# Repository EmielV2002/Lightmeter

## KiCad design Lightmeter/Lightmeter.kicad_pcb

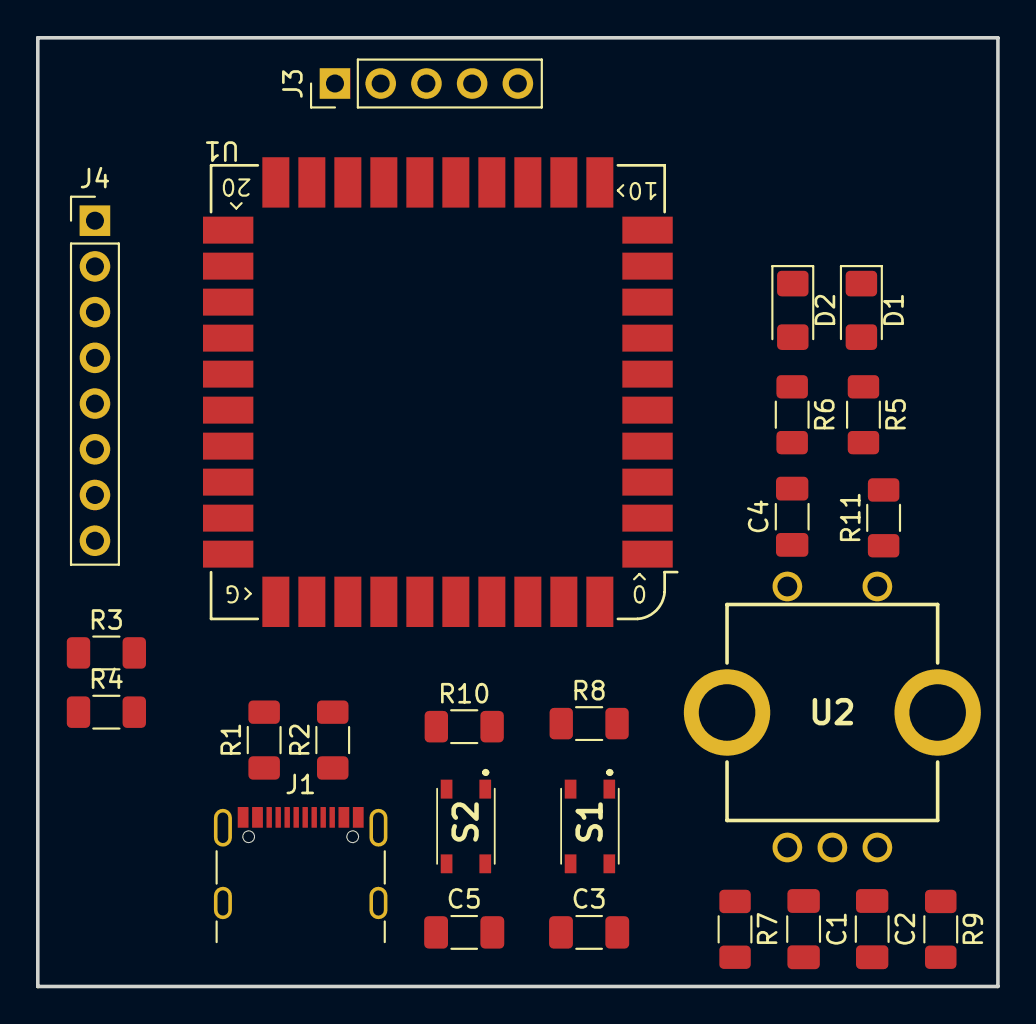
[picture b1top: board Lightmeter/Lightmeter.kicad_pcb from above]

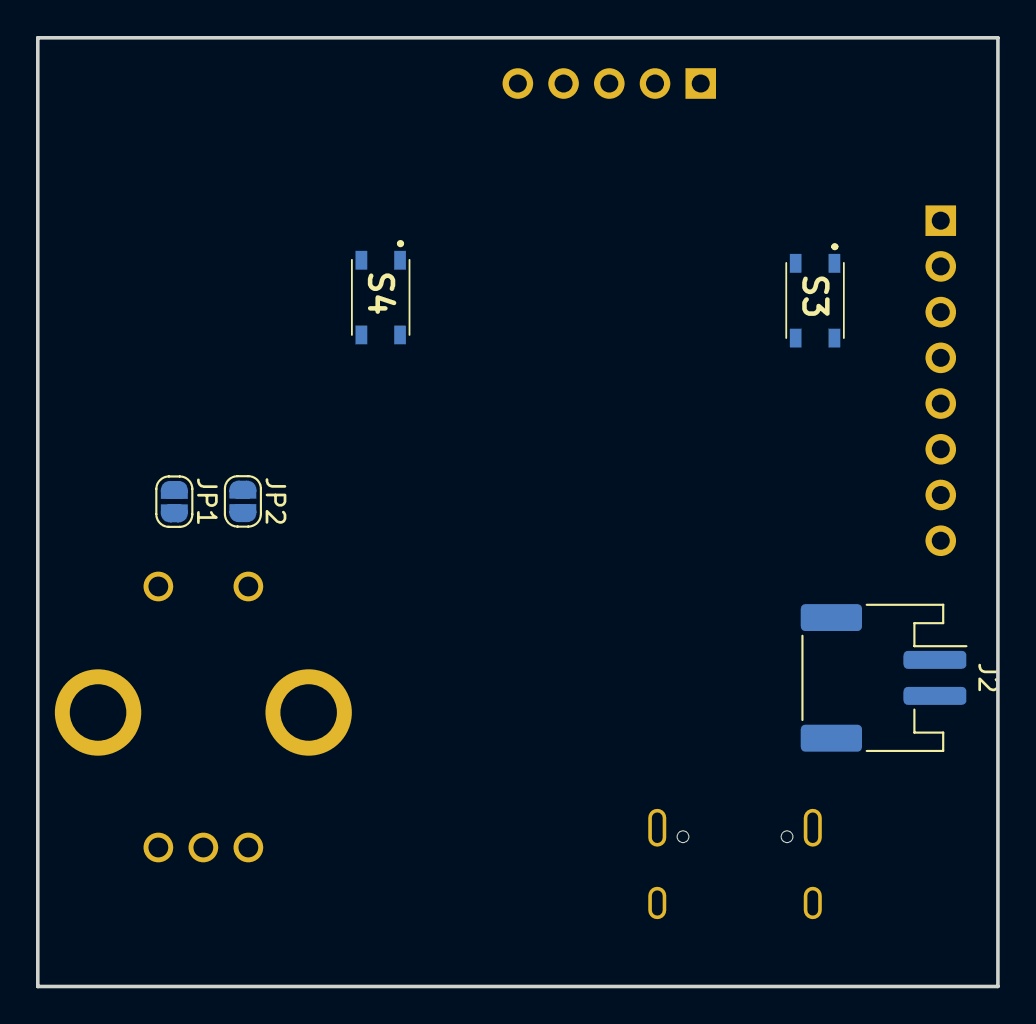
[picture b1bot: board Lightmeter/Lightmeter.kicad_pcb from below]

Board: 2 copper layers, 53.3 x 52.7 mm, 30 parts (5 on the bottom side), 30 nets, no tracks yet.

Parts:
C1, C2, C3, C4, C5: 0.1uF; C_1206_3216Metric_Pad1.33x1.80mm_HandSolder
D1, D2: LED; LED_1206_3216Metric_Pad1.42x1.75mm_HandSolder
J1: USB_C_Receptacle_USB2.0; USB_C_Receptacle_GCT_USB4105-xx-A_16P_TopMnt_Horizontal
J2: Conn_01x02_Socket; JST_PH_S2B-PH-SM4-TB_1x02-1MP_P2.00mm_Horizontal
J3: Conn_01x05_Pin; PinHeader_1x05_P2.54mm_Vertical
J4: Conn_01x08_Socket; PinHeader_1x08_P2.54mm_Vertical
JP1, JP2: Jumper_2_Open; SolderJumper-2_P1.3mm_Open_RoundedPad1.0x1.5mm
R1, R2: 5.1k; R_1206_3216Metric_Pad1.30x1.75mm_HandSolder
R3, R4: 100k; R_1206_3216Metric_Pad1.30x1.75mm_HandSolder
R5, R6: 1k; R_1206_3216Metric_Pad1.30x1.75mm_HandSolder
R7, R8, R9, R10, R11: 10k; R_1206_3216Metric_Pad1.30x1.75mm_HandSolder
S1, S2, S3, S4: PTS810SJK250SMTRLFS; PTS810SJG250SMTRLFS
U1: RP2040_Stamp; RP2040_Stamp_SMD
U2: EC11E1544505

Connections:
+3.3V: J3.5, J4.1, JP1.2 (B), JP2.2 (B), R7.2, R8.1, R9.2, R10.1, R11.2, U1.34 (3.3V)
+BATT: J2.1, R3.1, U1.32 (VBAT)
/BOOTSEL: S3.1, S3.2, U1.40 (BOOTSEL)
/EN_CLK: C1.1, R7.1, U1.8 (GPIO7), U2.1 (A)
/EN_DT: C2.1, R9.1, U1.9 (GPIO8), U2.2 (B)
/EN_SW: C4.1, R11.1, U1.10 (GPIO9), U2.4 (D)
/ISO: R8.2, S1.1, S1.2, U1.24 (GPIO23)
/LED_USR: D2.1 (K), U1.25 (GPIO24)
/L_SCL: J3.3, U1.6 (GPIO5)
/L_SDA: J3.4, U1.5 (GPIO4)
/MEAS: R10.2, S2.1, S2.2, U1.17 (GPIO16)
/SCREEN_CS: J4.6, U1.19 (GPIO18)
/SCREEN_DC: J4.7, U1.22 (GPIO21)
/SCREEN_MOSI: J4.4, U1.21 (GPIO20)
/SCREEN_RST: J4.8, U1.23 (GPIO22)
/SCREEN_SCK: J4.5, U1.20 (GPIO19)
/USB_D+: J1.A6 (D+), J1.B6 (D+), U1.36 (USB_D+)
/USB_D-: J1.A7 (D-), J1.B7 (D-), U1.35 (USB_D-)
/VDIV: R3.2, R4.1, U1.27 (GPIO26)
/~RESET: S4.1, S4.2, U1.39 (~RESET)
GNDREF: C1.2, C2.2, C3.2, C4.2, C5.2, D1.1 (K), J1.A1 (GND), J1.A12 (GND), J1.B1 (GND), J1.B12 (GND), J1.S1 (SHIELD), J2.2, J3.1, J4.2, R1.2, R2.2, R4.2, S3.3, S3.4, S4.3, S4.4, U1.31 (GND), U2.3 (C), U2.5 (E)
unnamed: C3.1, S1.3, S1.4
unnamed: C5.1, S2.3, S2.4
unnamed: D1.2 (A), R5.2
unnamed: D2.2 (A), R6.2
unnamed: J1.A5 (CC1), R1.1
unnamed: J1.B5 (CC2), R2.1
unnamed: JP1.1 (A), R5.1
unnamed: JP2.1 (A), R6.1
VBUS: J1.A4 (VBUS), J1.A9 (VBUS), J1.B4 (VBUS), J1.B9 (VBUS)

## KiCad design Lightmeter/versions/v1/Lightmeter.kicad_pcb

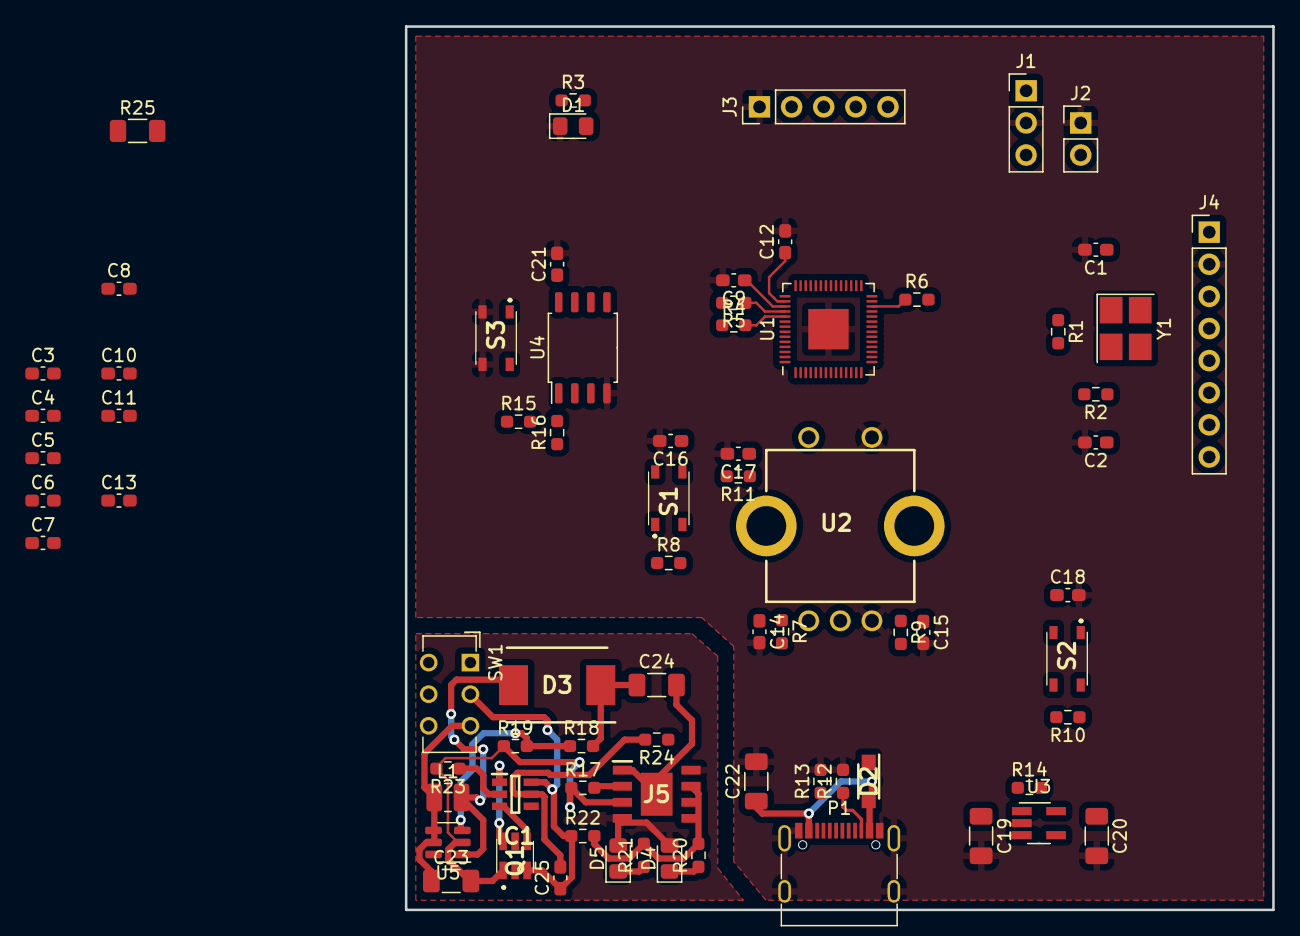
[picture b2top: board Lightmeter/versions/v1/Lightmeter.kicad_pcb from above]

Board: 2 copper layers, 68.6 x 69.8 mm, 74 parts (0 on the bottom side), 55 nets.

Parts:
C1, C2: 27pF; C_0603_1608Metric_Pad1.08x0.95mm_HandSolder
C3, C4, C5, C6, C7, C8, C10, C11, C13, C14, C15, C16, C17, C18, C21, C25: 0.1uF; C_0603_1608Metric_Pad1.08x0.95mm_HandSolder
C9, C12: 1uF; C_0603_1608Metric_Pad1.08x0.95mm_HandSolder
C19, C20: 1uF; C_1206_3216Metric_Pad1.33x1.80mm_HandSolder
C22: 10uF; C_1206_3216Metric_Pad1.33x1.80mm_HandSolder
C23, C24: 22uF; C_1206_3216Metric_Pad1.33x1.80mm_HandSolder
D1, D4, D5: LED; LED_0805_2012Metric_Pad1.15x1.40mm_HandSolder
D2: MBR120LSFT1G; SODFL3616X98N
D3: SS34; DIOM7959X262N
IC1: FS312F-G; SOT95P280X145-6N
J1: Conn_01x03_Socket; PinHeader_1x03_P2.54mm_Vertical
J2: Conn_01x02_Pin; PinHeader_1x02_P2.54mm_Vertical
J3: Conn_01x05_Pin; PinHeader_1x05_P2.54mm_Vertical
J4: Conn_01x08_Socket; PinHeader_1x08_P2.54mm_Vertical
J5: TP4056; SOIC127P600X175-9N
L1: 22uH; L_1008_2520Metric
P1: USB_C_Plug_USB2.0; USB_C_Receptacle_G-Switch_GT-USB-7010ASV
Q1: FS8205
R1: DNP; R_0603_1608Metric_Pad0.98x0.95mm_HandSolder
R2, R3, R15, R19, R20, R21: 1k; R_0603_1608Metric_Pad0.98x0.95mm_HandSolder
R4, R5: 27; R_0603_1608Metric_Pad0.98x0.95mm_HandSolder
R6, R7, R8, R9, R10, R11, R14, R16: 10k; R_0603_1608Metric_Pad0.98x0.95mm_HandSolder
R12, R13: 5.1k 1%; R_0603_1608Metric_Pad0.98x0.95mm_HandSolder
R17: 2k; R_0603_1608Metric_Pad0.98x0.95mm_HandSolder
R18: 7.5k; R_0603_1608Metric_Pad0.98x0.95mm_HandSolder
R22, R23, R24: 100; R_0603_1608Metric_Pad0.98x0.95mm_HandSolder
R25: 10k; R_1206_3216Metric_Pad1.30x1.75mm_HandSolder
S1, S2, S3: PTS810SJK250SMTRLFS; PTS810SJG250SMTRLFS
SW1: SW_DPDT_x2; SW_CuK_JS202011AQN_DPDT_Angled
U1: RP2040; QFN-56-1EP_7x7mm_P0.4mm_EP3.2x3.2mm
U2: EC11E1544505
U3: AP2112K-3.3; SOT-23-5_HandSoldering
U4: W25Q32JVSS; SOIC-8_5.23x5.23mm_P1.27mm
U5: MT3608; SOT-23-6
Y1: Crystal; Crystal_SMD_3225-4Pin_3.2x2.5mm_HandSoldering

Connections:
+3.3V: C3.1, C4.1, C5.1, C6.1, C7.1, C8.1, C10.1, C20.1, C21.1, J3.5, J4.1, R6.2, R7.2, R8.2, R9.2, R10.2, R11.2, R16.1, U1.1 (IOVDD), U1.10 (IOVDD), U1.22 (IOVDD), U1.33 (IOVDD), U1.42 (IOVDD), U1.43 (ADC_AVDD), U1.48 (USB_VDD), U1.49 (IOVDD), U3.5 (VOUT), U4.8 (VCC)
+5V: C22.1, D2.2, D4.2 (A), D5.2 (A), J5.4 (VCC4), J5.8 (CE), P1.A4 (VBUS), P1.A9 (VBUS), P1.B4 (VBUS), P1.B9 (VBUS)
/+1.1V: C11.1, C13.1, U1.23 (DVDD), U1.50 (DVDD)
/EN_CLK: C14.1, R7.1, U1.8 (GPIO6), U2.1 (A)
/EN_DT: C15.1, R9.1, U1.9 (GPIO7), U2.2 (B)
/EN_SW: C17.1, R11.1, U1.11 (GPIO8), U2.4 (D)
/Flash/USB_BOOT: R15.1, S3.1, S3.2
/GPIO25: R3.1, U1.37 (GPIO25)
/ISO: R8.1, S1.1, S1.2, U1.34 (GPIO22)
/L_SCL: J3.3, U1.5 (GPIO3)
/L_SDA: J3.4, U1.4 (GPIO2)
/LiPo/BAT: C25.1, IC1.6 (GND), Q1.3 (S2), R22.1, SW1.2 (B)
/MEAS: R10.1, S2.1, S2.2, U1.18 (GPIO15)
/Power/VSYS: C19.1, C24.1, D2.1, D3.1, R14.1, R18.2, U3.1 (VIN)
/QSPI_CS: R15.2, R16.2, U1.56 (QSPI_SS), U4.1 (~CS)
/QSPI_SCK: U1.52 (QSPI_SCLK), U4.6 (CLK)
/QSPI_SD0: U1.53 (QSPI_SD0), U4.5 (DI(IO0))
/QSPI_SD1: U1.55 (QSPI_SD1), U4.2 (DO(IO1))
/QSPI_SD2: U1.54 (QSPI_SD2), U4.3 (IO2)
/QSPI_SD3: U1.51 (QSPI_SD3), U4.7 (IO3)
/RUN: J2.2, R6.1, U1.26 (RUN)
/SCREEN_CS: J4.6, U1.28 (GPIO17)
/SCREEN_DC: J4.7, U1.31 (GPIO20)
/SCREEN_MOSI: J4.4, U1.30 (GPIO19)
/SCREEN_RST: J4.8, U1.32 (GPIO21)
/SCREEN_SCK: J4.5, U1.29 (GPIO18)
/SWCLK: J1.1, U1.24 (SWCLK)
/SWDIO: J1.3, U1.25 (SWD)
/USB_N: P1.A7 (D-), R5.2
/USB_P: P1.A6 (D+), R4.1
/XIN: C1.1, R1.1, U1.20 (XIN), Y1.1
/XOUT: R1.2, R2.2, U1.21 (XOUT)
GNDREF: C1.2, C2.2, C3.2, C4.2, C5.2, C6.2, C7.2, C8.2, C9.2, C10.2, C11.2, C12.2, C13.2, C14.2, C15.2, C16.2, C17.2, C18.2, C19.2, C20.2, C21.2, C22.2, C23.2, C24.2, D1.1 (K), J1.2, J2.1, J3.1, J4.2, J5.1 (TEMP1), J5.3 (GND_3), J5.9 (EP), P1.A1 (GND), P1.A12 (GND), P1.B1 (GND), P1.B12 (GND), P1.S1 (SHIELD), Q1.1 (S1), R12.2, R13.2, R17.1, R19.1, R23.2, S3.3, S3.4, U1.19 (TESTEN), U1.57 (GND), U2.3 (C), U2.5 (E), U3.2 (GND), U4.4 (GND), U5.2 (GND)
unnamed: C2.1, R2.1, Y1.2
unnamed: C16.1, S1.3, S1.4
unnamed: C18.1, S2.3, S2.4
unnamed: D1.2 (A), R3.2
unnamed: D4.1 (K), R20.1
unnamed: D5.1 (K), R21.1
unnamed: IC1.2 (CS), R23.1
unnamed: IC1.3 (OC), Q1.6 (G1)
unnamed: IC1.1 (OD), Q1.4 (G2)
unnamed: C25.2, IC1.5 (VCC), R24.2
unnamed: J5.5 (BAT), J5.6 (~STDBY), J5.7 (~CHRG), R20.2, R21.2, R22.2
unnamed: J5.2 (PROG2), R17.2
unnamed: P1.A5 (CC), R13.1
unnamed: P1.B5 (VCONN), R12.1
unnamed: C23.1, L1.1, SW1.3 (C), U5.4 (EN), U5.5 (IN)
unnamed: R5.1, U1.46 (USB_DM)
unnamed: R4.2, U1.47 (USB_DP)
unnamed: C12.1, U1.44 (VREG_IN)
unnamed: C9.1, U1.45 (VREG_VOUT)
unnamed: R14.2, U3.3 (EN)
unnamed: R18.1, R19.2, U5.3 (FB)
unnamed: D3.2, L1.2, U5.1 (SW)
